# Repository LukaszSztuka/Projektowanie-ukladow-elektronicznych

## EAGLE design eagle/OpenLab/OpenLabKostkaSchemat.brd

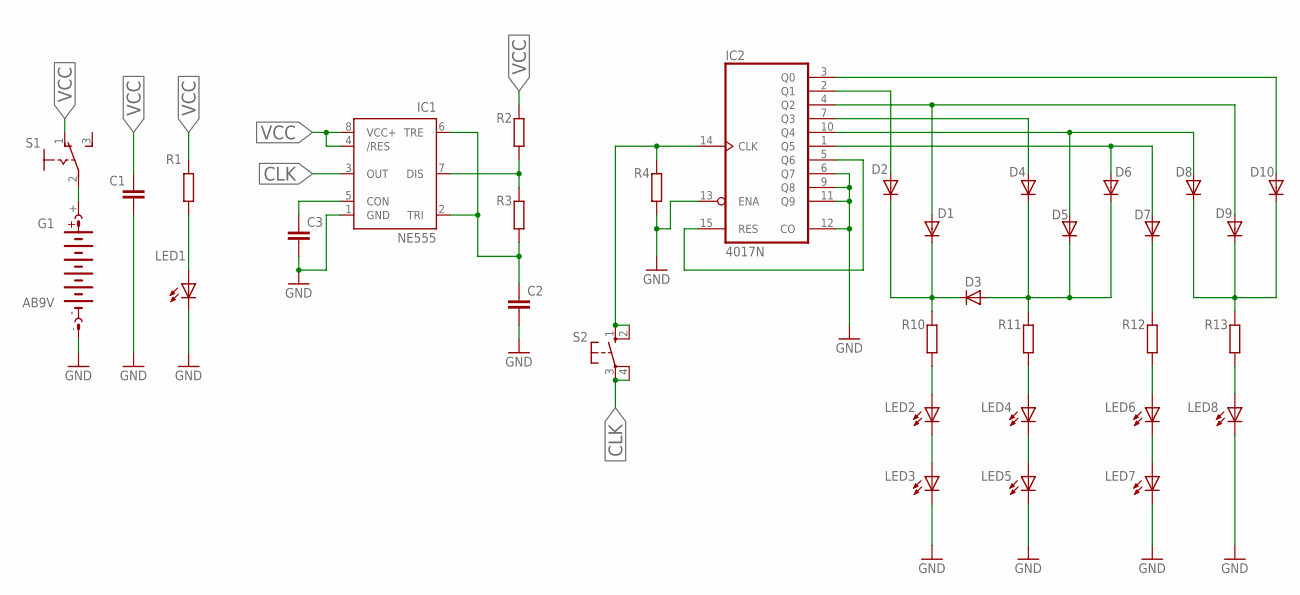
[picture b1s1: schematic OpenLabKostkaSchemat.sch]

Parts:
C1, C2, C3: C5/2.5; C5B2.5
D1, D2, D3, D4, D5, D6, D7, D8, D9, D10: 1N4446; DO35-10
G1: AB9V
IC1: NE555; DIL-08
IC2: 4017N; DIL16
LED1, LED2, LED3, LED4, LED5, LED6, LED7, LED8: LED_ELD260; LED_LD260
R1, R2, R3, R4, R10, R11, R12, R13: R0204/7; 0204/7
S1: 255SB
S2: 10-XX; B3F-10XX

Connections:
CLK: IC1.3 (OUT), S2.3, S2.4 (P1)
GND: C1.1, C2.2, C3.2, G1.-, IC1.1 (GND), IC2.6 (Q7), IC2.9 (Q8), IC2.11 (Q9), IC2.12 (CO), IC2.13 (ENA), LED1.K (C), LED3.K (C), LED5.K (C), LED7.K (C), LED8.K (C), R4.1
unnamed: C2.1, IC1.2 (TRI), IC1.6 (TRE), R3.1
unnamed: IC2.14 (CLK), R4.2, S2.1 (S), S2.2 (S1)
unnamed: LED2.K (C), LED3.A
unnamed: IC1.7 (DIS), R2.1, R3.2
unnamed: D8.C, D9.C, D10.C, R13.2
unnamed: LED4.K (C), LED5.A
unnamed: LED6.K (C), LED7.A
unnamed: D10.A, IC2.3 (Q0)
unnamed: G1.+, S1.2
unnamed: D2.A, IC2.2 (Q1)
unnamed: LED1.A, R1.1
unnamed: LED8.A, R13.1
unnamed: LED6.A, R12.1
unnamed: LED4.A, R11.1
unnamed: LED2.A, R10.1
unnamed: D7.C, R12.2
unnamed: D3.A, D4.C, D5.C, D6.C, R11.2
unnamed: C3.1, IC1.5 (CON)
unnamed: D1.A, D9.A, IC2.4 (Q2)
unnamed: IC2.5 (Q6), IC2.15 (RES)
unnamed: D4.A, IC2.7 (Q3)
unnamed: D5.A, D8.A, IC2.10 (Q4)
unnamed: D6.A, D7.A, IC2.1 (Q5)
unnamed: D1.C, D2.C, D3.C, R10.2
VCC: C1.2, IC1.4 (/RES), IC1.8 (VCC+), R1.2, R2.2, S1.1 (O)
VDD: IC2.16 (VDD)
VSS: IC2.8 (VSS)

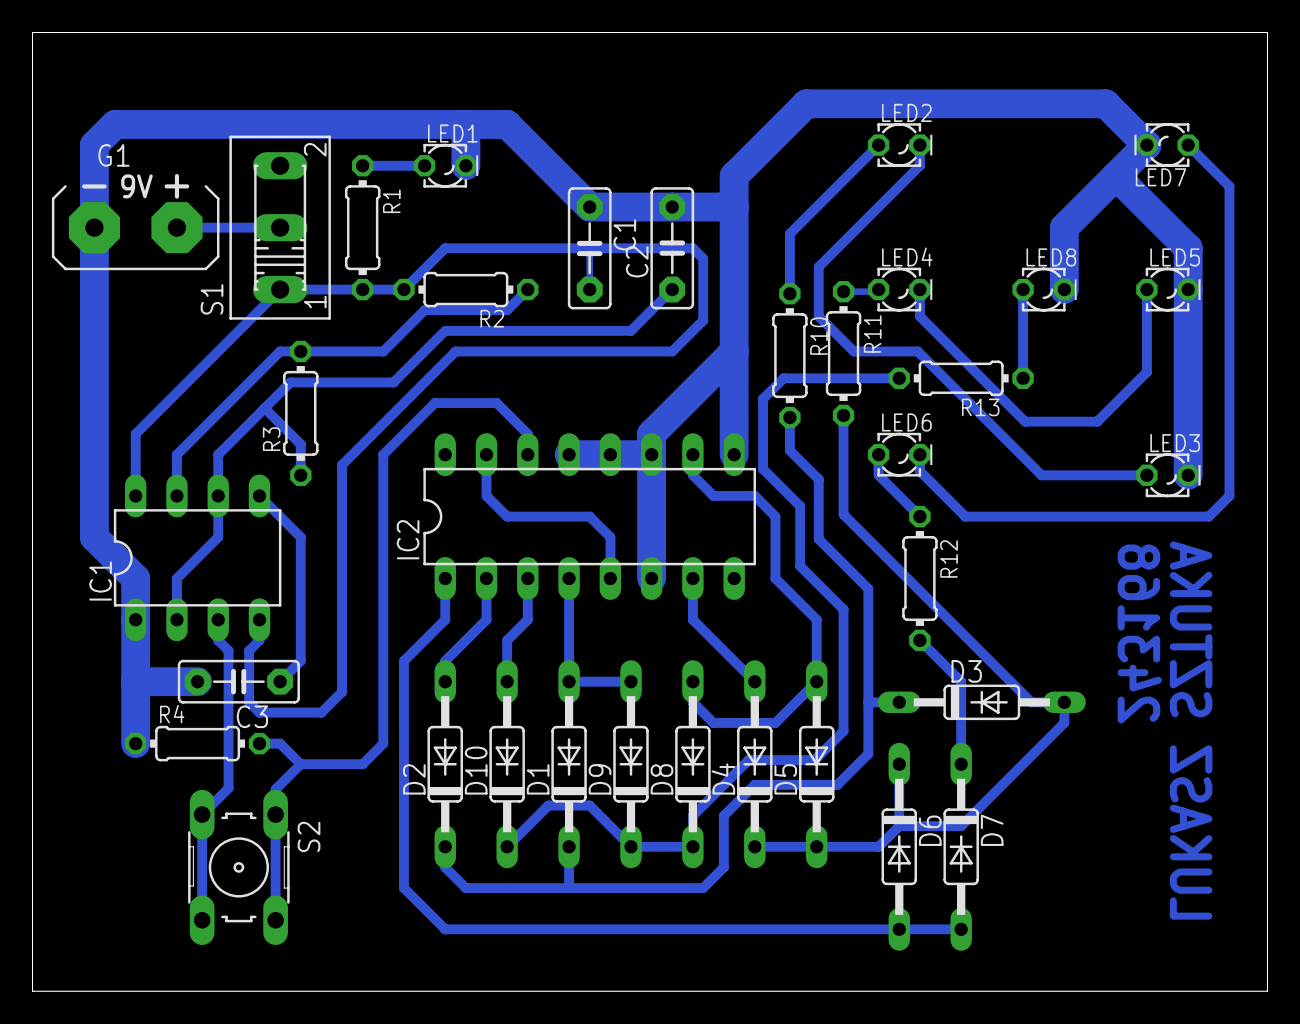
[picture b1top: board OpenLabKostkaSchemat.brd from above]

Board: 2 copper layers, 76.0 x 59.0 mm, 34 parts (0 on the bottom side), 27 nets.

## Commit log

2022-03-09 Adding all files
